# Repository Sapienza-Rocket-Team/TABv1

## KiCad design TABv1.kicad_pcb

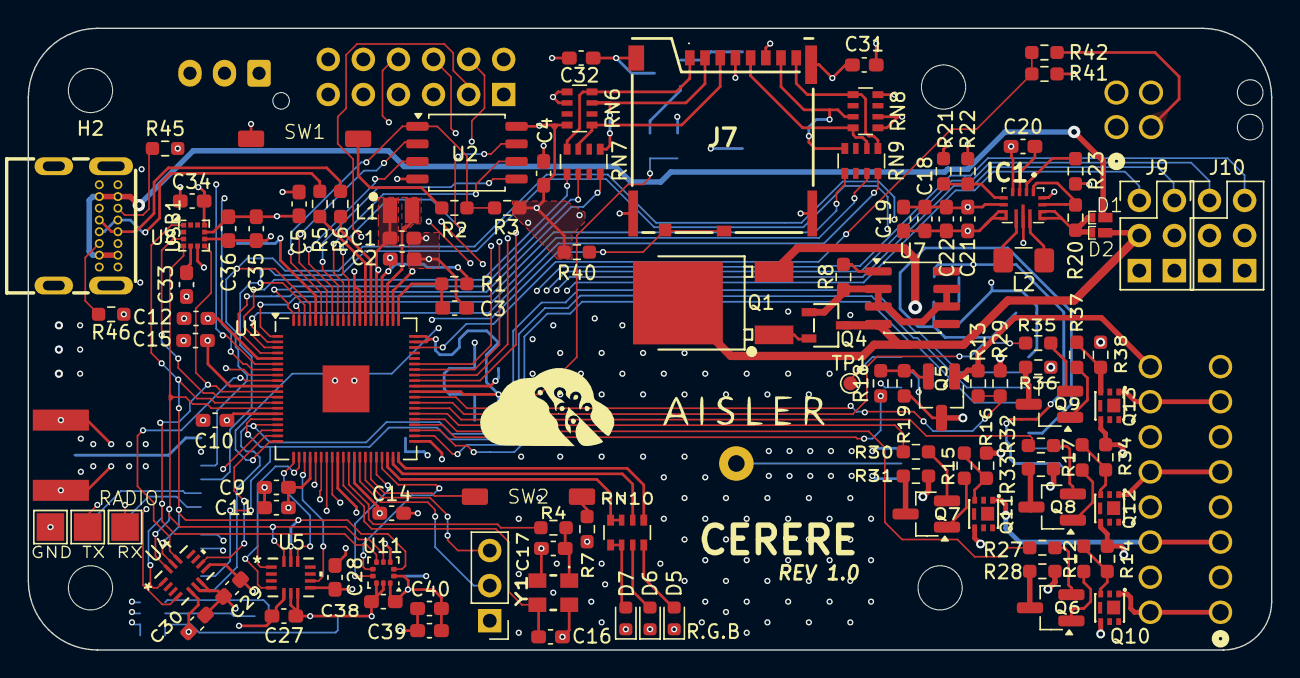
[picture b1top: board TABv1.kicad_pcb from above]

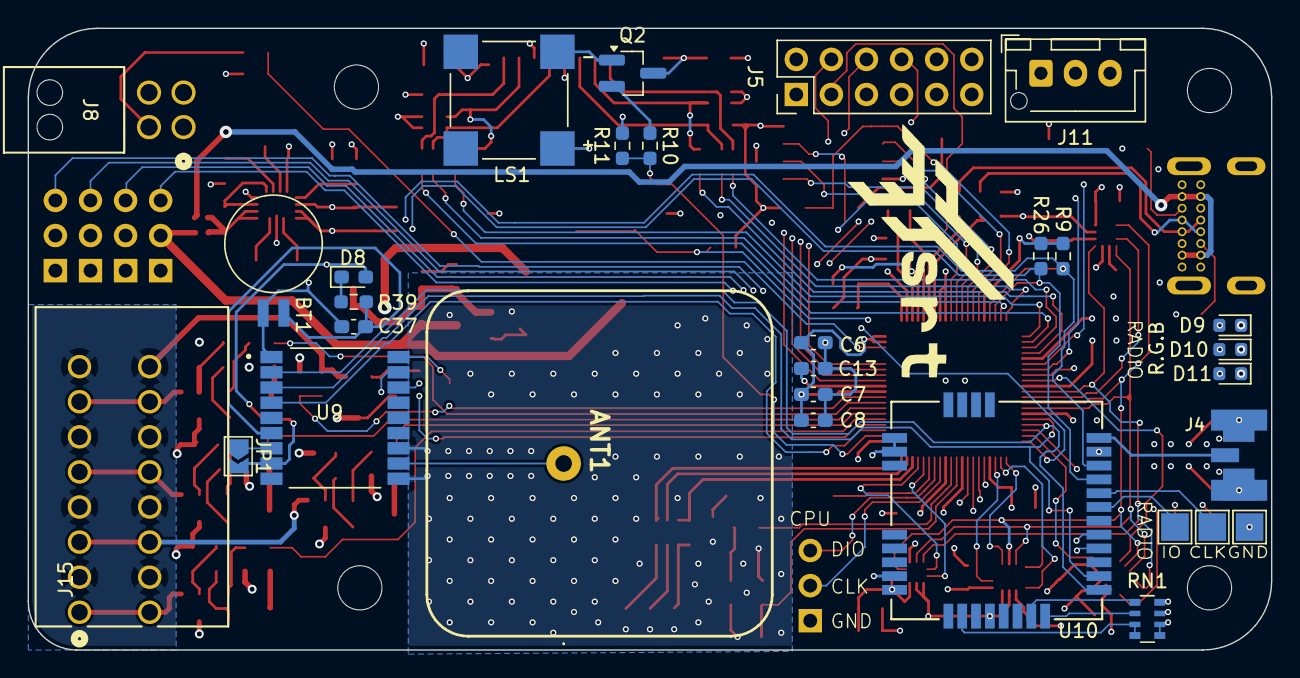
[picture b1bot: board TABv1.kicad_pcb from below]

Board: 4 copper layers, 90.0 x 45.0 mm, 145 parts (30 on the bottom side), 134 nets.

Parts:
ANT1: AANI-PP-0055; AANIPP0055
BT1: Battery_Cell; BatteryHolder_Seiko_MS621F
C1, C2, C3: 4.7uF; C_0603_1608Metric_Pad1.08x0.95mm_HandSolder
C4, C5, C6, C7, C8, C9, C10, C11, C12, C13, C14, C15: 100n; C_0603_1608Metric_Pad1.08x0.95mm_HandSolder
C16, C17: 15pF; C_0603_1608Metric_Pad1.08x0.95mm_HandSolder
C18, C19, C22: 22uF; C_0603_1608Metric_Pad1.08x0.95mm_HandSolder
C20, C27, C28, C29, C30, C31, C37, C38, C40: 100nF; C_0603_1608Metric_Pad1.08x0.95mm_HandSolder
C21, C32, C35: 10uF; C_0603_1608Metric_Pad1.08x0.95mm_HandSolder
C33: 220nF; C_0603_1608Metric_Pad1.08x0.95mm_HandSolder
C34, C36: 100nf; C_0603_1608Metric_Pad1.08x0.95mm_HandSolder
C39: 10nF; C_0603_1608Metric_Pad1.08x0.95mm_HandSolder
D1, D2: D_Schottky_Small; SDM2U30CSP
D5, D9: BLUE; LED_0603_1608Metric
D6, D10: GREEN; LED_0603_1608Metric
D7, D11: RED; LED_0603_1608Metric
D8: D_Schottky_Small; D_0603_1608Metric_Pad1.05x0.95mm_HandSolder
H1, H2, H3, H4: MountingHole; MountingHole_3.2mm_M3
IC1: TPS630702RNMR; TPS630701RNMR
J4: Conn_Coaxial; SMA_EDGE__UFL
J5: Conn_02x06_Counter_Clockwise; PinHeader_2x06_P2.54mm_Vertical
J6: SWD; PinHeader_1x03_P2.54mm_Vertical
J7: 503398-1892; 5033981892
J8: 1053141104; CONN_SD-105314-100_04_MOL
J9, J10: Conn_02x03_Odd_Even; PinHeader_2x03_P2.54mm_Vertical
J11: Conn_UART_1; JST_XH_B3B-XH-AM_1x03_P2.50mm_Vertical
J15: DB141R-2.54-8P-GN; CONN16_DB141R_DIO
JP1: SolderJumper_2_Open; SolderJumper-2_P1.3mm_Open_TrianglePad1.0x1.5mm
L1: 3.3uh directional; L_AOTA-B201610S3R3-101-T_MCH
L2: 1.5uh; L_1206_3216Metric_Pad1.42x1.75mm_HandSolder
LS1: CMT-8503-85B-SMT-TR; XDCR_CMT-8503-85B-SMT-TR
Q1: MJD44H11T4G; TO-252-2_L6.5-W6.1-P4.58-LS10.0-TL
Q2, Q5, Q6, Q7, Q8, Q9: NMOS; SOT-23_Handsoldering
Q4: BC817-25,215; SOT-23-3_L2.9-W1.6-P1.90-LS2.8-BR
Q10, Q11, Q12, Q13: PJM09P30DF; DFN-6_L2.0-W2.0-P0.65-BL-EP-1
R1: 33; R_0603_1608Metric_Pad0.98x0.95mm_HandSolder
R2, R4, R7, R12, R15, R17, R18, R27, R30, R32, R35, R37: 1k; R_0603_1608Metric_Pad0.98x0.95mm_HandSolder
R3, R14, R16, R19, R20, R28, R29, R31, R33, R34, R36, R38, R40, R41: 10k; R_0603_1608Metric_Pad0.98x0.95mm_HandSolder
R5, R6: 27; R_0603_1608Metric_Pad0.98x0.95mm_HandSolder
R8: 430; R_0603_1608Metric_Pad0.98x0.95mm_HandSolder
R9, R26: 4.7k; R_0603_1608Metric_Pad0.98x0.95mm_HandSolder
R10: 100; R_0603_1608Metric_Pad0.98x0.95mm_HandSolder
R11: 10K; R_0603_1608Metric_Pad0.98x0.95mm_HandSolder
R13, R42: 40k; R_0603_1608Metric_Pad0.98x0.95mm_HandSolder
R21: 470k; R_0603_1608Metric_Pad0.98x0.95mm_HandSolder
R22: 150k; R_0603_1608Metric_Pad0.98x0.95mm_HandSolder
R23: 100k; R_0603_1608Metric_Pad0.98x0.95mm_HandSolder
R39: 47k; R_0603_1608Metric_Pad0.98x0.95mm_HandSolder
R45, R46: 5.1k; R_0603_1608Metric_Pad0.98x0.95mm_HandSolder
RN1, RN10: 220; R_Array_Convex_4x0603
RN6, RN8: 24k; R_Array_Convex_4x0603
RN7, RN9: 47; R_Array_Convex_4x0603
SW1: BOOTSEL; TSB008
SW2: RESET; TSB008
TP1: TestPoint; TestPoint_Pad_D1.0mm
TP2, TP3, TP4, TP5, TP6, TP7: TestPoint_Flag; TestPoint_Pad_2.0x2.0mm
U1: RP2350B-QFN80; QFN-80-1EP_10x10mm_P0.4mm_EP3.4x3.4mm
U2: W25Q128JVS; SOIC-8_5.3x5.3mm_P1.27mm
U4, U5: LSM6DSV80XTR; QFN_LSM6DSV80XTR_STM
U7: LM334M; SOIC-8_3.9x4.9mm_P1.27mm
U8: LIS2MDL; LGA-12_2x2mm_P0.5mm
U9: TESEO-LIV4F; XCVR_TESEO-LIV4F
U10: RAK3172; RAK3172_RAK
U11: LPS22DF; ST_HLGA-10_2x2mm_P0.5mm_LayoutBorder3x2y
USB1: TYPEC-306DDW-ARP16; USB-C-TH_TYPEC-306DDW-ARP16
Y1: 12MHz; ABM8272T3

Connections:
+1V1: C1.1, C13.2, C14.2, C15.2, L1.1, U1.10 (DVDD), U1.32 (DVDD), U1.51 (DVDD), U1.65 (VREG_FB)
+3V3: C2.1, C4.1, C5.2, C6.2, C7.2, C8.2, C9.2, C10.2, C11.2, C12.2, C18.1, C19.1, C21.2, C22.1, C27.2, C28.2, C29.2, C30.2, C31.1, C32.2, C34.1, C35.1, C36.2, C38.1, C39.1, C40.1, D8.2 (A), IC1.7 (VOUT_1), IC1.8 (VOUT_2), J5.2, J7.4 (VDD), JP1.2 (B), LS1.P, R1.2, R3.1, R9.2, R21.2, R23.1, R26.2, R40.1, RN6.5 (R4.2), RN6.6 (R3.2), RN6.8 (R1.2), RN8.5 (R4.2), RN8.6 (R3.2), RN8.8 (R1.2), U1.5 (IOVDD), U1.15 (IOVDD), U1.24 (IOVDD), U1.29 (IOVDD), U1.41 (IOVDD), U1.50 (IOVDD), U1.59 (ADC_AVDD), U1.60 (IOVDD), U1.64 (VREG_VIN), U1.68 (USB_OTP_VDD), U1.69 (QSPI_IOVDD), U1.76 (IOVDD), U2.8 (VCC), U4.5, U4.8, U5.5, U5.8, U8.9 (Vdd), U8.10 (Vdd_IO), U9.8 (VCC), U10.24 (VDD), U11.1 (Vdd_IO), U11.10 (VDD)
+BATT: D2.2 (A), J8.3, J9.3, J9.4, J10.3, J10.4, Q1.4 (C), Q4.3, R42.2, U7.4
/AVDD: C3.2, R1.1, U1.61 (VREG_AVDD)
/BARO_CS: U1.37 (GPIO29), U11.6 (~CS)
/BARO_INT: U1.36 (GPIO28), U11.7 (INT_DRDY)
/BATT_SENSE: R41.2, R42.1, U1.58 (GPIO47_ADC7)
/BUZZ: R10.1, R11.2, U1.42 (GPIO33)
/GPIO20: J5.3, U1.20 (GPIO20)
/GPIO41: J5.4, U1.52 (GPIO41_ADC1)
/GPIO42: J5.6, U1.53 (GPIO42_ADC2)
/GPIO43: J5.8, U1.54 (GPIO43_ADC3)
/GPIO44: J5.10, U1.55 (GPIO44_ADC4)
/IMU45_CS: U1.9 (GPIO11), U4.12
/IMU45_INT1: U1.18 (GPIO18), U4.4
/IMU45_INT2: U1.19 (GPIO19), U4.9
/IMU_CS: U1.21 (GPIO21), U5.12
/IMU_INT1: U1.22 (GPIO22), U5.4
/IMU_INT2: U1.23 (GPIO23), U5.9
/LX: L1.2, U1.63 (VREG_LX)
/L_BLUE: RN10.1 (R1.1), U1.40 (GPIO32)
/L_GREEN: RN10.2 (R2.1), U1.39 (GPIO31)
/L_RED: RN10.3 (R3.1), RN10.4 (R4.1), U1.38 (GPIO30)
/LoRa & GPS/L_BLUE: RN1.1 (R1.1), U10.31 (PB4/ADC2)
/LoRa & GPS/L_GREEN: RN1.2 (R2.1), U10.32 (PB3/ADC1)
/LoRa & GPS/L_RED: RN1.3 (R3.1), RN1.4 (R4.1), U10.26 (PB2/AD3)
/LoRa & GPS/SWCLK: TP4.1, U10.8 (PA14/SWCLK)
/LoRa & GPS/SWDIO: TP3.1, U10.7 (PA13/SWDIO)
/MAG_CS: U1.12 (GPIO13), U8.3 (~CS)
/PWM1: J5.11, J10.2, U1.25 (GPIO24)
/PWM2: J5.9, J10.1, U1.26 (GPIO25)
/PWM3: J5.7, J9.2, U1.27 (GPIO26)
/PWM4: J5.5, J9.1, U1.28 (GPIO27)
/PYRO_ENABLE: R18.1, U1.44 (GPIO35)
/PYRO_FIRE_1: R27.1, U1.45 (GPIO36)
/PYRO_FIRE_2: R30.1, U1.46 (GPIO37)
/PYRO_FIRE_3: R32.1, U1.47 (GPIO38)
/PYRO_FIRE_4: R35.1, U1.48 (GPIO39)
/PYRO_SENSE: R13.1, R29.2, U1.49 (GPIO40_ADC0)
/Pyro/PYRO1: J15.1, J15.9, Q10.1 (D)
/Pyro/PYRO2: J15.3, J15.11, Q11.1 (D)
/Pyro/PYRO3: J15.5, J15.13, Q12.1 (D)
/Pyro/PYRO4: J15.7, J15.15, Q13.1 (D)
/Pyro/PYRO_HIGH: Q1.3 (E), Q10.4 (S), Q11.4 (S), Q12.4 (S), Q13.4 (S), R14.2, R16.2, R34.2, R38.2
/Pyro/PYRO_LOW: J15.2, J15.4, J15.6, J15.8, J15.10, J15.12, J15.14, J15.16, Q5.1 (D), R13.2
/QSPI Flash/~USB_BOOT: R2.1, SW1.2
/RESET: SW2.2, U1.35 (RUN)
/RX_GPS: U1.16 (GPIO16), U9.3 (UART-RX), U10.2 (PA2/UART2_TX)
/SCLK: U1.71 (QSPI_SCLK), U2.6 (CLK)
/SCL_RADIO: R26.1, U1.78 (GPIO1), U9.17 (I2C_SCL), U10.9 (PA12/I2C_SCL)
/SD0: U1.72 (QSPI_SD0), U2.5 (DI/IO_{0})
/SD1: U1.74 (QSPI_SD1), U2.2 (DO/IO_{1})
/SD2: U1.73 (QSPI_SD2), U2.3 (~WP/IO_{2})
/SD3: U1.70 (QSPI_SD3), U2.7 (~HOLD/~RESET/IO_{3})
/SDA_RADIO: R9.1, U1.77 (GPIO0), U9.16 (I2C_SDA), U10.10 (PA11/I2C_SDA)
/SD_CLK: RN9.7 (R2.2), U1.79 (GPIO2)
/SD_CMD: RN7.6 (R3.2), U1.80 (GPIO3)
/SD_DAT0: RN9.5 (R4.2), U1.1 (GPIO4)
/SD_DAT1: RN9.8 (R1.2), U1.2 (GPIO5)
/SD_DAT2: RN7.5 (R4.2), U1.3 (GPIO6)
/SD_DAT3: RN7.8 (R1.2), U1.4 (GPIO7)
/SD_detect: J7.9 (DETECT_LEVER), J7.10 (DETECT_SWITCH), R40.2, U1.8 (GPIO10)
/SPI1.CK: U1.13 (GPIO14), U4.13, U5.13, U8.1 (SCL/SPC), U11.2 (SCL)
/SPI1.RX: U1.11 (GPIO12), U4.1, U5.1, U8.7 (DRDY), U11.5 (SA0)
/SPI1.TX: U1.14 (GPIO15), U4.14, U5.14, U8.4 (SDA/SDI/SDO), U11.4 (SDA)
/SS: R2.2, R3.2, U1.75 (QSPI_SS), U2.1 (~CS)
/TX_GPS: U1.17 (GPIO17), U9.2 (UART-TX), U10.1 (PA3/UART2_RX)
/XIN: C16.2, U1.30 (XIN), Y1.3
/XOUT: R4.1, U1.31 (XOUT)
/microSD/_DAT1: J7.8 (DAT1), RN8.1 (R1.1), RN9.1 (R1.1)
/microSD/_DAT2: J7.1 (DAT2), RN6.4 (R4.1), RN7.4 (R4.1)
/microSD/_DAT3: J7.2 (CD/DAT3), RN6.3 (R3.1), RN7.1 (R1.1)
ANT: J4.1 (In), U10.12 (RF)
D+: R5.2, USB1.A6 (DP1), USB1.B6 (DP2)
D-: R6.2, USB1.A7 (DN1), USB1.B7 (DN2)
GND: BT1.2 (-), C1.2, C2.2, C3.1, C4.2, C5.1, C6.1, C7.1, C8.1, C9.1, C10.1, C11.1, C12.1, C13.1, C14.1, C15.1, C16.1, C17.1, C18.2, C19.2, C20.1, C21.1, C22.2, C27.1, C28.1, C29.1, C30.1, C31.2, C32.1, C33.2, C34.2, C35.2, C36.1, C37.2, C38.2, C39.2, C40.2, D5.1 (K), D6.1 (K), D7.1 (K), D9.1 (K), D10.1 (K), D11.1 (K), IC1.4 (GND), IC1.6 (FB2), IC1.10 (PGND), IC1.15 (VSEL), J4.2 (Ext), J5.1, J5.12, J6.1, J7.6 (VSS), J7.11, J7.12, J7.13, J7.14, J8.4, J9.5, J9.6, J10.5, J10.6, J11.1, Q2.3 (S), Q5.3 (S), R7.1, R11.1, R19.1, R22.1, R28.1, R29.1, R31.1, R33.1, R36.1, R41.1, R45.2, R46.2, SW1.1, TP2.1, TP5.1, U1.62 (VREG_PGND), U1.81 (GND), U2.4 (GND), U4.6, U4.7, U5.6, U5.7, U8.6 (GND), U8.8 (GND), U9.1 (GND), U9.10 (GND_RF), U9.12 (GND_RF__1), U10.11 (GND), U10.17 (GND), U10.18 (GND), U10.23 (GND), U10.28 (GND), U11.3 (GND), U11.8 (GND_IO), U11.9 (GND), USB1.17 (EH), USB1.18 (EH), USB1.19 (EH), USB1.20 (EH), USB1.A1 (GND), USB1.A12 (GND), USB1.B1 (GND), USB1.B12 (GND), Y1.2, Y1.4
unnamed: BT1.1 (+), C37.1, R39.2, U9.6 (VBAT)
unnamed: C17.2, R4.2, Y1.1
unnamed: D1.1 (K), D2.1 (K), IC1.12 (VIN_1), IC1.13 (VIN_2), R20.2
unnamed: D5.2 (A), RN10.8 (R1.2)
unnamed: D6.2 (A), RN10.7 (R2.2)
unnamed: D7.2 (A), RN10.5 (R4.2), RN10.6 (R3.2)
unnamed: D8.1 (K), R39.1
unnamed: D9.2 (A), RN1.8 (R1.2)
unnamed: D10.2 (A), RN1.7 (R2.2)
unnamed: D11.2 (A), RN1.5 (R4.2), RN1.6 (R3.2)
unnamed: IC1.5 (FB), R21.1, R22.2
unnamed: IC1.11 (L1), L2.2
unnamed: IC1.9 (L2), L2.1
unnamed: C20.2, IC1.3 (VAUX)
unnamed: J6.2, U1.33 (SWCLK)
unnamed: J6.3, U1.34 (SWDIO)
unnamed: J7.5 (CLK), RN8.4 (R4.1), RN9.2 (R2.1)
unnamed: J7.3 (CMD), RN6.1 (R1.1), RN7.3 (R3.1)
unnamed: J7.7 (DAT0), RN8.3 (R3.1), RN9.4 (R4.1)
unnamed: J11.2, U1.7 (GPIO9)
unnamed: J11.3, U1.6 (GPIO8)
unnamed: JP1.1 (A), U9.7 (RESERVED)
unnamed: Q1.1 (B), Q4.2
unnamed: LS1.N, Q2.1 (D)
unnamed: Q2.2 (G), R10.2
unnamed: Q4.1, R8.2, U7.2, U7.3, U7.6, U7.7
unnamed: Q5.2 (G), R18.2, R19.2
unnamed: Q6.1 (D), R12.1
unnamed: Q6.2 (G), R27.2
unnamed: Q6.3 (S), R28.2
unnamed: Q7.1 (D), R15.1
unnamed: Q7.2 (G), R30.2
unnamed: Q7.3 (S), R31.2
unnamed: Q8.1 (D), R17.1
unnamed: Q8.2 (G), R32.2
unnamed: Q8.3 (S), R33.2
unnamed: Q9.1 (D), R37.1
unnamed: Q9.2 (G), R35.2
unnamed: Q9.3 (S), R36.2
unnamed: Q10.3 (G), R12.2, R14.1
unnamed: Q11.3 (G), R15.2, R16.1
unnamed: Q12.3 (G), R17.2, R34.1
unnamed: Q13.3 (G), R37.2, R38.1
unnamed: R7.2, SW2.1
unnamed: R8.1, U7.1
unnamed: R45.1, USB1.A5 (CC1)
unnamed: R46.1, USB1.B5 (CC2)
unnamed: R6.1, U1.66 (USB_DM)
unnamed: R5.1, U1.67 (USB_DP)
unnamed: C33.1, U8.5 (C1)
unnamed: TP1.1, U9.18 (PRG)
unnamed: ANT1.1, U9.11 (RF_IN)
unnamed: TP6.1, U10.4 (PB6/UART1_TX)
unnamed: TP7.1, U10.5 (PB7/UART1_RX)
PG: IC1.2 (PG), R23.2
PPS: U1.43 (GPIO34), U9.4 (PPS)
SYNC: IC1.1 (PS/SYNC), IC1.14 (EN), R20.1
VUSB: D1.2 (A), USB1.A4 (VBUS), USB1.A9 (VBUS), USB1.B4 (VBUS), USB1.B9 (VBUS)

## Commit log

2025-09-19 inizio TABv1
2025-09-26 update blocco pyro
    scelta pmos e bjt
2025-09-27 bozza layout pcb
2025-10-04 ridimensionamento scheda
2025-10-04 ridimensionamento scheda
    to do:
    - aggiungere led rgb smd
    - gps
    - can bus
    - lora/altro
2025-10-11 inserimento servo
2025-10-18 led e buzzer
2025-10-25 Modifica radio/gps
2025-10-25 footprint modulo radio
2025-10-25 Comunicazione Pico - GPS/Radio
2025-10-25 L1 footprint updated
2025-10-25 commit di prova
2025-10-25 elimino file buttare
2025-10-25 aggiunte tracce per regolatore spostato gnd plane al secondo layer e messo 3v3 al rpimo layer aggiunto f courtyard su bootsel switch (sw1)
2025-10-29 Lora radio and gps small additions
2025-10-30 Corrections
2025-10-31 NET allignment (all on +3V3)
2025-10-31 RC-WLE5-434 aggiunta induttanza
2025-11-08 New GPS and sensors
2025-11-15 LIV5
2025-11-15 minor corrections
2025-11-15 lib allign
2025-11-15 libs
2025-11-15 lib allignment
2025-11-22 inizio routing rp2350
2025-11-22 update routing
2025-11-22 continuo routing
2025-11-29 Aggiornamento routing
2025-11-29 Aggiunte footprint/schematiche Molex
2025-11-29 sma fix
2025-11-29 fix continuo
2025-11-29 upload routing con rotellini
2025-11-30 Ulteriori modifiche routing
    Idea di layout pyro
2025-12-03 Changes meeting 03/12
2025-12-03 ultime change routing pyro
2025-12-03 wiring parte pyro
2025-12-05 minor_changes
2025-12-05 small_changes
2025-12-06 Routing Changes
2025-12-06 ROUTING
2025-12-06 Routing 06/25
    Molte modifiche
2025-12-06 mega routing sensori led e 5v usb
2025-12-06 Modifiche del sabato sera
    Molto Routing
2025-12-07 Un paio di (piccole) modifiche
2025-12-11 Small changes
2025-12-11 Changes 11/12
2025-12-13 changes sat 13/12/25
2025-12-13 small
2025-12-14 Collegamenti ultimati
2025-12-18 Modifiche 18/12
2025-12-18 changes 18/12
2025-12-20 changes 20/12
2025-12-20 ROBE
2025-12-20 Aggiunta regolatore tensione ST
    Ho aggiunto il regolatore di tensione ST L6983NQTR, ho fatto le connessioni richieste, ho iniziato il piazzamento dei componenti.
    Entro domani in serata dovrei ultimare
2025-12-20 Ulteriori Modifiche
2025-12-25 silkscreeen fix
2025-12-26 Names fix
2026-01-10 10/01/2025
    1v1 fix and v regulator final decision, general BOM corrections and allignments
2026-01-12 Small changes
    modified Main LEDs.
    Added Radio LEDs.
    Connected the GPS uart to the Radio.
    Added a test point for the GPS PRG pin.
    Modified the Pyro current limiter for better BOM compliance.
    Modified a copule of estetic things on the schematic.
2026-01-13 Small details
    Added SWD test point for the Radio.
    Added UART test point for the Radio.
    Connected the GPS to the radio trough UART.
    Fixed names around the board.
    Checked the Crystal capacitance (OK).
2026-01-15 Last fixes
    Added i2c connection to gps.
    Added test point for swd and Uart for radio.
    check footprint compatibility between liv3f and liv4f.
    ... Other ...
2026-01-15 Changed USB (before first order)
    changed USB footprint to new one.
    Added the CC pull-downs to garantee power delivery.
    Other small details.
